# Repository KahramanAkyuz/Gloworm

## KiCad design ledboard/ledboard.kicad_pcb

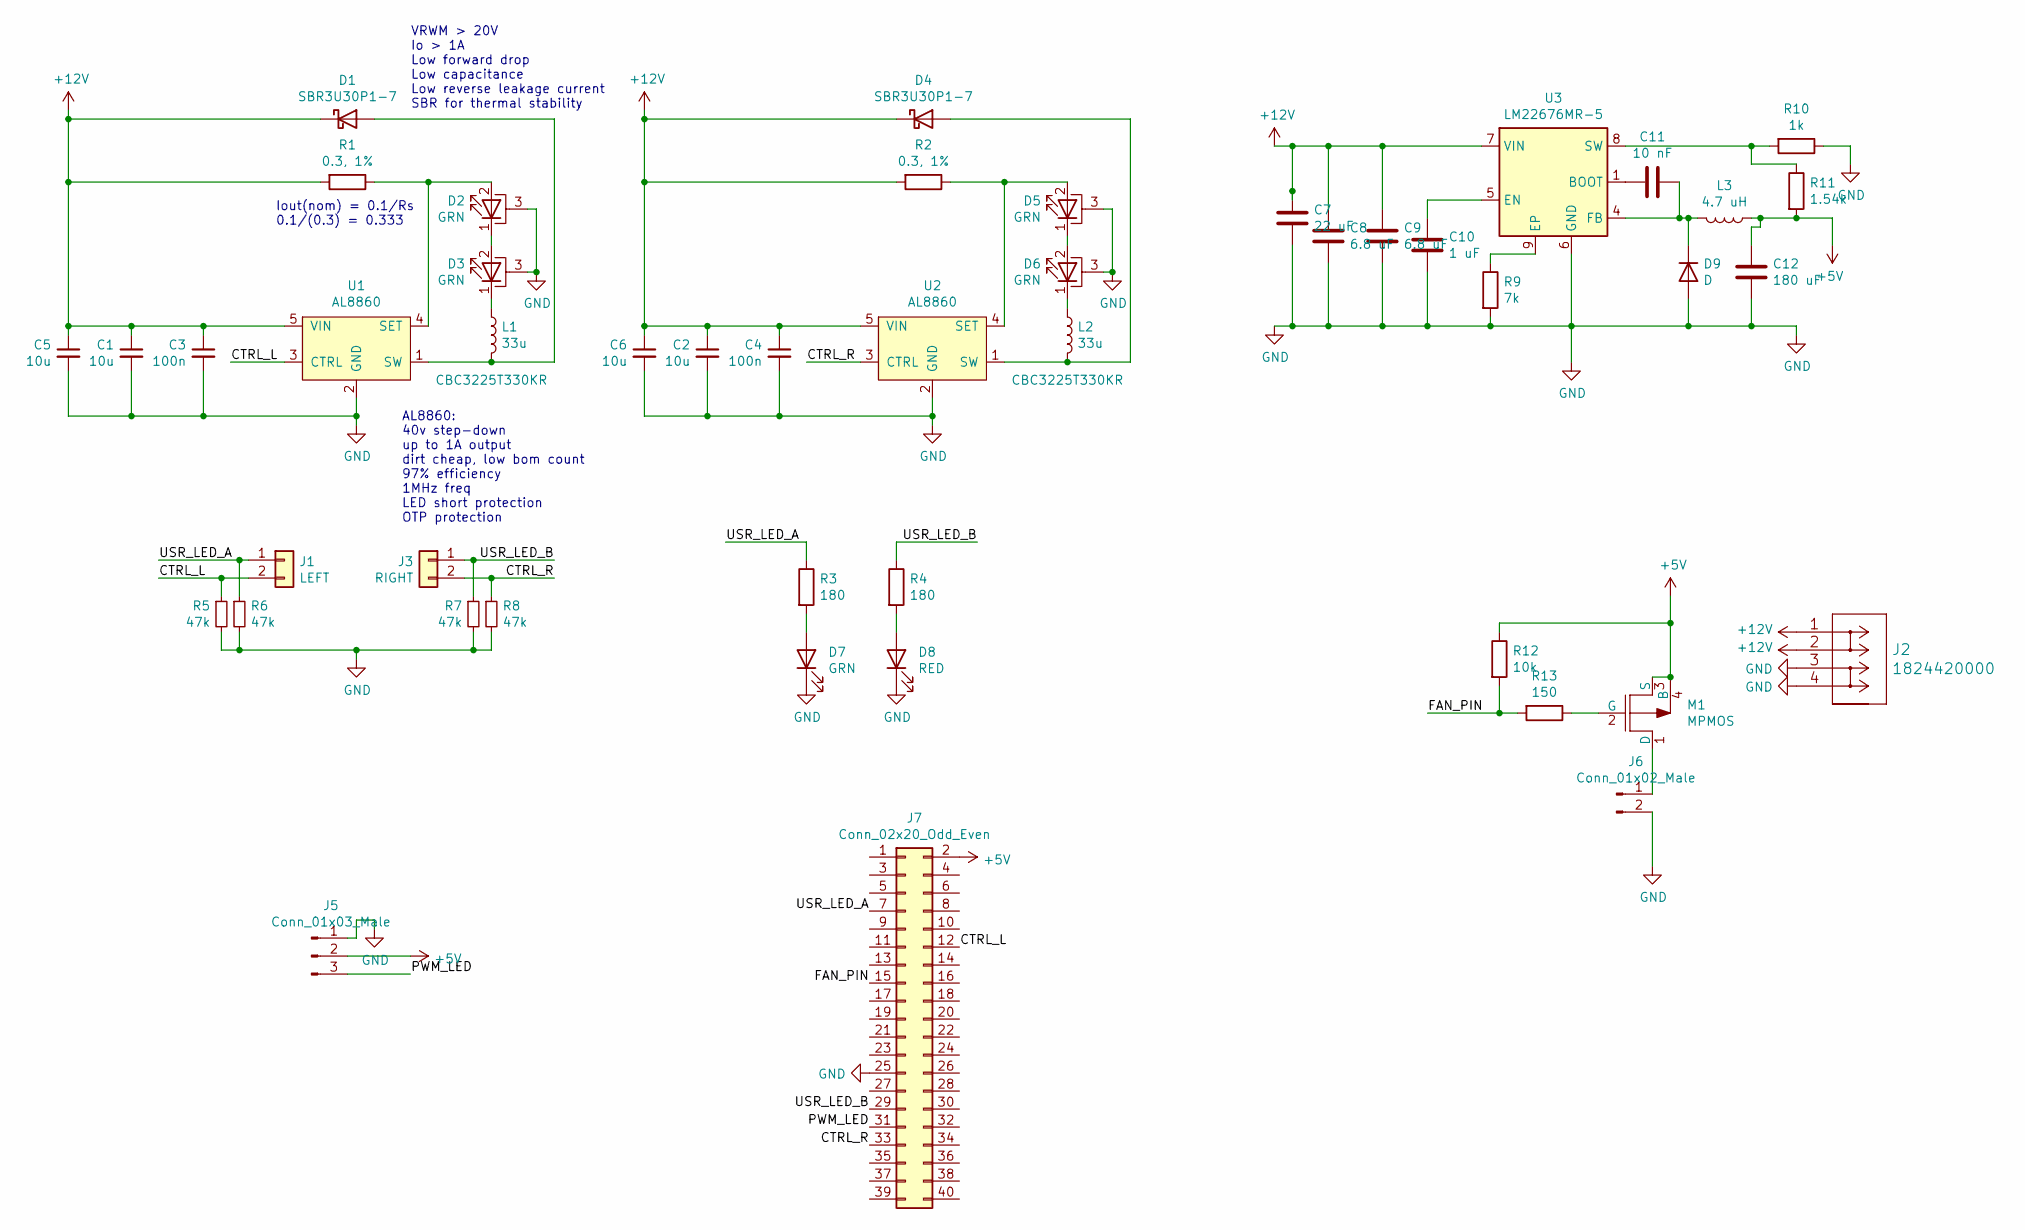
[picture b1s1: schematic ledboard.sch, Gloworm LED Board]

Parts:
C1, C2, C5, C6: 10u; C_0603_1608Metric; LCSC C96446
C3, C4: 100n; C_0402_1005Metric; LCSC C106256
C7: 22 uF; C_0805_2012Metric_Pad1.15x1.40mm_HandSolder
C8, C9: 6.8 uF; C_0805_2012Metric_Pad1.15x1.40mm_HandSolder
C10: 1 uF; C_0805_2012Metric_Pad1.15x1.40mm_HandSolder
C11: 10 nF; C_0805_2012Metric_Pad1.15x1.40mm_HandSolder
C12: 180 uF; CP_Radial_D6.3mm_P2.50mm
D1, D4: SBR3U30P1-7; D_PowerDI-123; LCSC C110517
D2, D3, D5, D6: GRN; LED_1W_3W_R8
D7: GRN; LTST-S220; LCSC C160470
D8: RED; LTST-S220; LCSC C284935
D9: D; D_0603_1608Metric_Pad1.05x0.95mm_HandSolder
J1: LEFT; PinHeader_1x02_P2.54mm_Vertical_RoundRect; LCSC C358684
J2: 1824420000
J3: RIGHT; PinHeader_1x02_P2.54mm_Vertical_RoundRect; LCSC C358684
J5: Conn_01x03_Male; PinHeader_1x03_P1.00mm_Horizontal
J6: Conn_01x02_Male; PinHeader_1x02_P1.00mm_Horizontal
J7: Conn_02x20_Odd_Even; PinHeader_2x20_P2.54mm_Vertical
L1, L2: 33u; L_1210_3225Metric; LCSC C223226
L3: 4.7 uH; C_0201_0603Metric
M1: MPMOS; TO-220-3_Vertical
R1, R2: 0.3, 1%; R_0805_2012Metric; LCSC C247157
R3, R4: 180; R_0402_1005Metric; LCSC C137913
R5, R6, R7, R8: 47k; R_0402_1005Metric; LCSC C25563
R9: 7k; R_0805_2012Metric_Pad1.15x1.40mm_HandSolder
R10: 1k; R_0603_1608Metric_Pad1.05x0.95mm_HandSolder
R11: 1.54k; R_0603_1608Metric_Pad1.05x0.95mm_HandSolder
R12: 10k; R_0805_2012Metric_Pad1.15x1.40mm_HandSolder
R13: 150; R_0805_2012Metric_Pad1.15x1.40mm_HandSolder
U1, U2: AL8860; TSOT-23-5_RoundRect; LCSC C125330
U3: LM22676MR-5; TI_SO-PowerPAD-8

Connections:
+5V: C12.1, J5.2, J7.2, L3.1, M1.3 (S), M1.4 (B), R11.2, R12.1
+12V: C1.1, C2.1, C3.1, C4.1, C5.1, C6.1, C7.1, C8.1, C9.1, D1.1 (K), D4.1 (K), J2.1, J2.2, R1.2, R2.2, U1.5 (VIN), U2.5 (VIN), U3.7 (VIN)
/CTRL_L: J1.2, J7.12, R5.1, U1.3 (CTRL)
/CTRL_R: J3.2, J7.33, R8.1, U2.3 (CTRL)
/FAN_PIN: J7.15, R12.2, R13.2
/PWM_LED: J5.3, J7.31
/USR_LED_A: J1.1, J7.7, R3.1, R6.1
/USR_LED_B: J3.1, J7.29, R4.1, R7.1
GND: C1.2, C2.2, C3.2, C4.2, C5.2, C6.2, C7.2, C8.2, C9.2, C10.2, C12.2, D2.3 (PAD), D3.3 (PAD), D5.3 (PAD), D6.3 (PAD), D7.1 (K), D8.1 (K), D9.2 (A), J2.3, J2.4, J5.1, J6.2, J7.25, R5.2, R6.2, R7.2, R8.2, R9.2, R10.1, U1.2 (GND), U2.2 (GND), U3.6 (GND)
unnamed: C10.1, U3.5 (EN)
unnamed: C11.1, D9.1 (K), L3.2, U3.4 (FB)
unnamed: C11.2, U3.1 (BOOT)
unnamed: D1.2 (A), L1.2, U1.1 (SW)
unnamed: D2.1 (K), D3.2 (A)
unnamed: D2.2 (A), R1.1, U1.4 (SET)
unnamed: D3.1 (K), L1.1
unnamed: D4.2 (A), L2.2, U2.1 (SW)
unnamed: D5.1 (K), D6.2 (A)
unnamed: D5.2 (A), R2.1, U2.4 (SET)
unnamed: D6.1 (K), L2.1
unnamed: D7.2 (A), R3.2
unnamed: D8.2 (A), R4.2
unnamed: J6.1, M1.1 (D)
unnamed: M1.2 (G), R13.1
unnamed: R9.1, U3.9 (EP)
unnamed: R10.2, R11.1, U3.8 (SW)

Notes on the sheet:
Iout(nom) = 0.1/Rs 0.1/(0.3) = 0.333
VRWM > 20V Io > 1A Low forward drop Low capacitance Low reverse leakage current SBR for thermal stability
AL8860: 40v step-down up to 1A output dirt cheap, low bom count 97% efficiency 1MHz freq LED short protection OTP protection

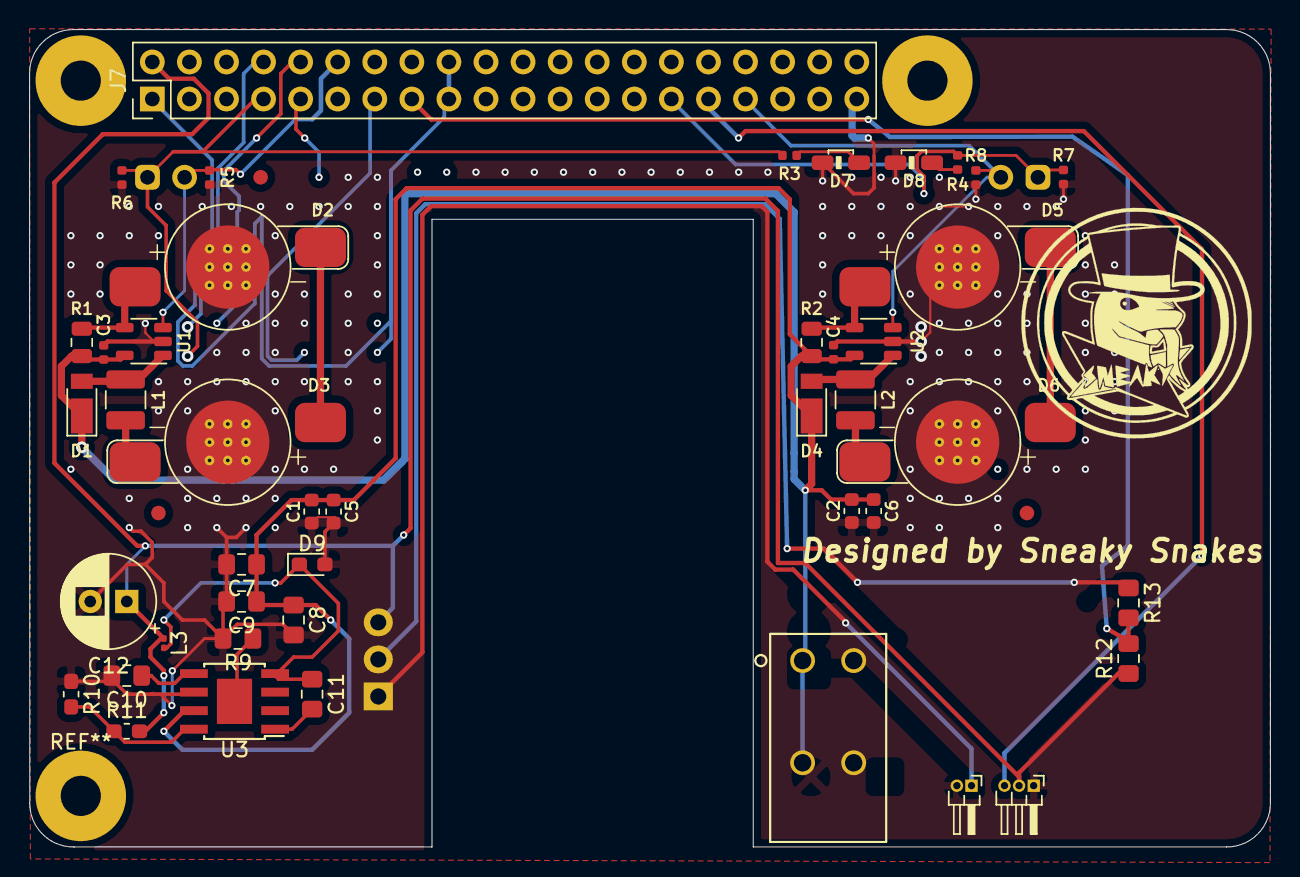
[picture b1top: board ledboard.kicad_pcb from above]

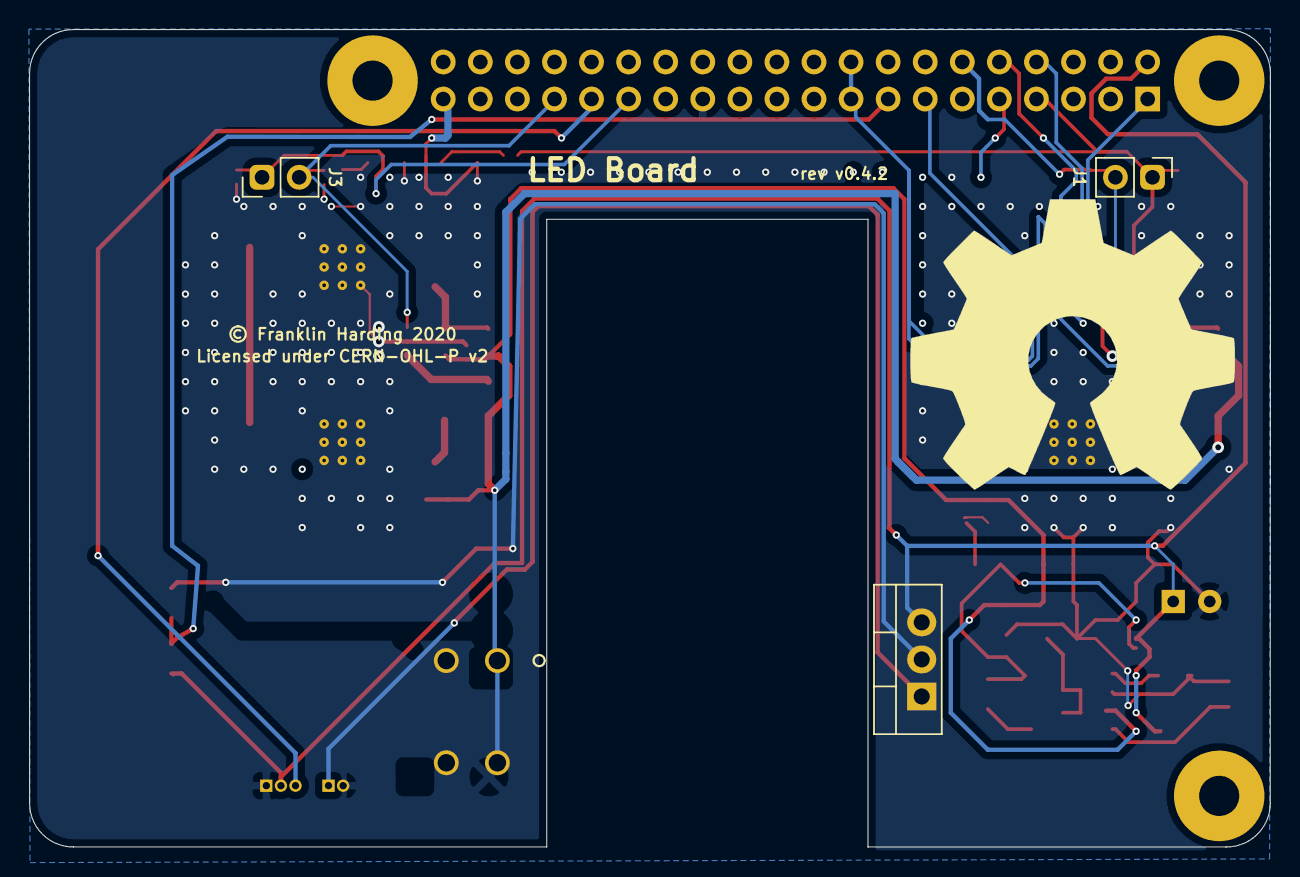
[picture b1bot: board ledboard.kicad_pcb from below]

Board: 2 copper layers, 85.0 x 56.0 mm, 50 parts (3 on the bottom side), 26 nets.

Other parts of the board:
FID1, FID2, FID3: Fiducial_1mm_Mask2mm

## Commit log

2020-10-09 modified :snake:
2020-10-25 last
2020-10-25 Gerber
2020-12-02 hole
2020-12-10 wire
2020-12-10 done
2020-12-15 Umarım son olur
2020-12-16 Kicadden nefret ediyorum
2020-12-28 power soket

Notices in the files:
ledboard/ledboard.kicad_pcb:
Copyright Franklin Harding 2020
Licensed under CERN-OHL-P v2
© Franklin Harding 2020
parts and their libraries:
Copyright 2016 Accelerated Designs. All rights reserved.
